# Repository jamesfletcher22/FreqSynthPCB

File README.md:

# FreqSynthPCB
A PCB Design for an Si5351A Frequency Synthesiser with Manual Control

This is a PCB I designed for a Si5351a Frequency Synthesiser. It can generate a clock at any arbitrary frequency with 1KHz resolution up to 125MHz.
Control is done using a ATMEGA328-PB. 
There is a rotary encoder to control the frequency at the output, along with an OLED for displaying the selected frequency

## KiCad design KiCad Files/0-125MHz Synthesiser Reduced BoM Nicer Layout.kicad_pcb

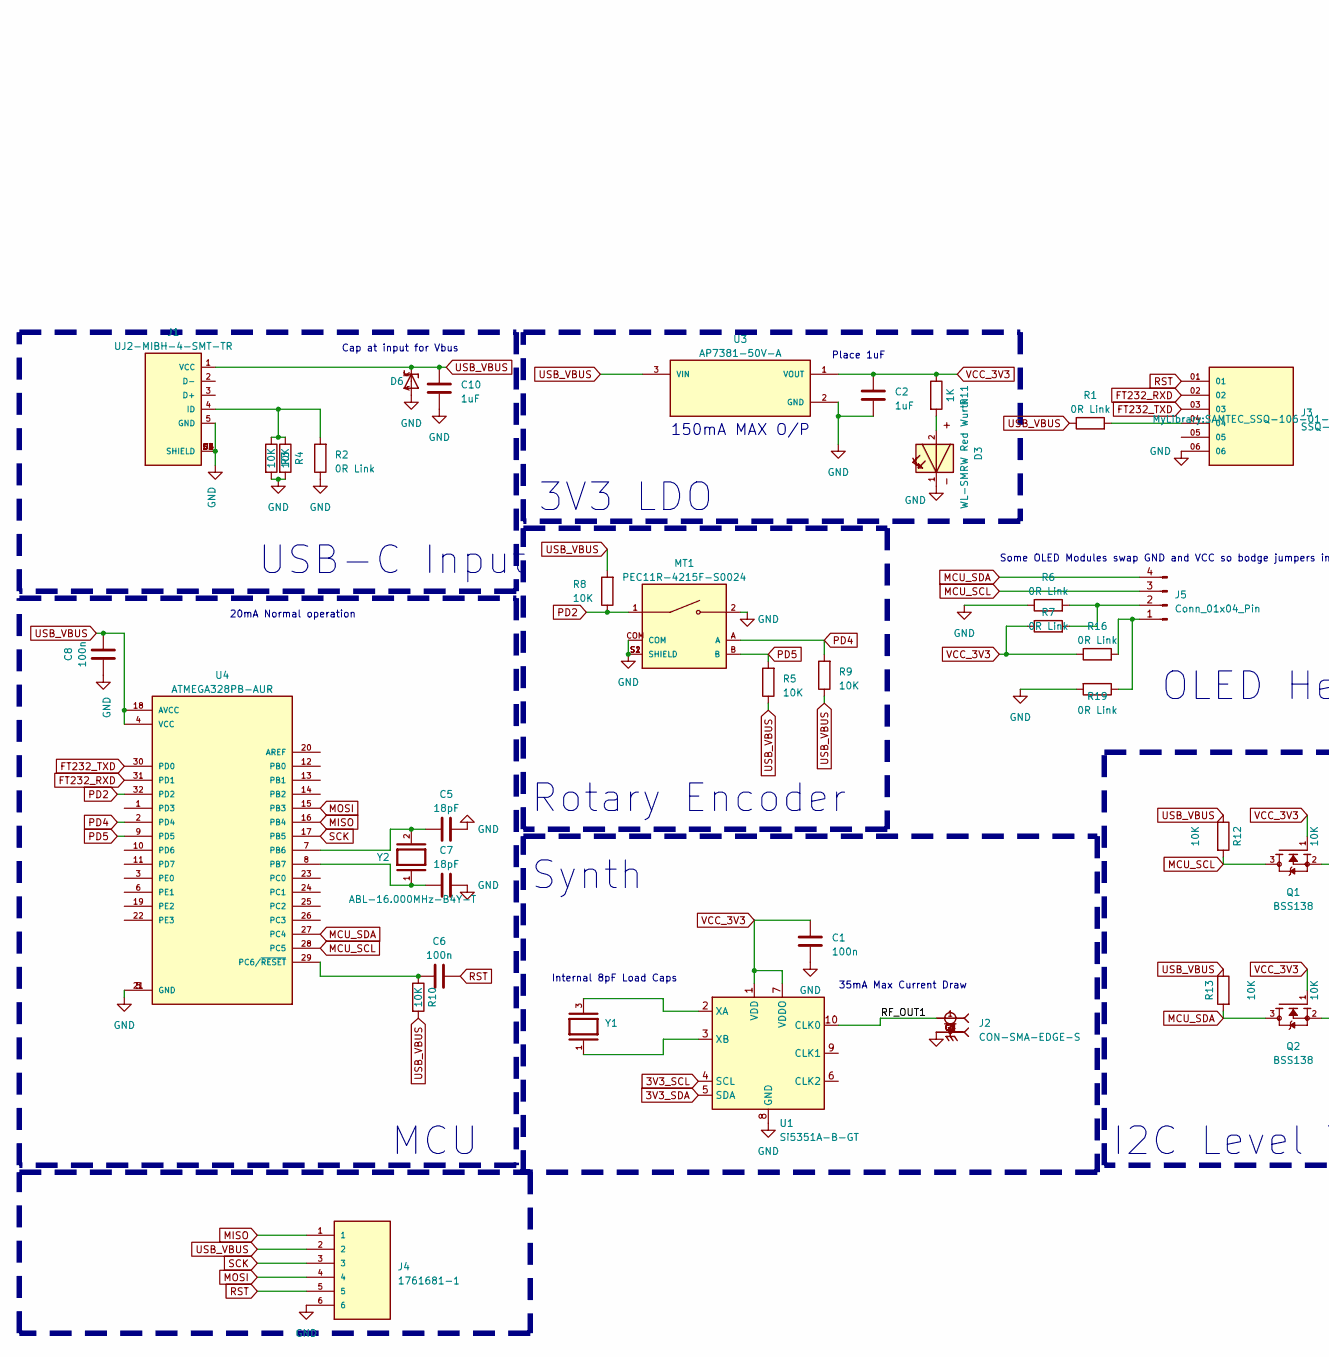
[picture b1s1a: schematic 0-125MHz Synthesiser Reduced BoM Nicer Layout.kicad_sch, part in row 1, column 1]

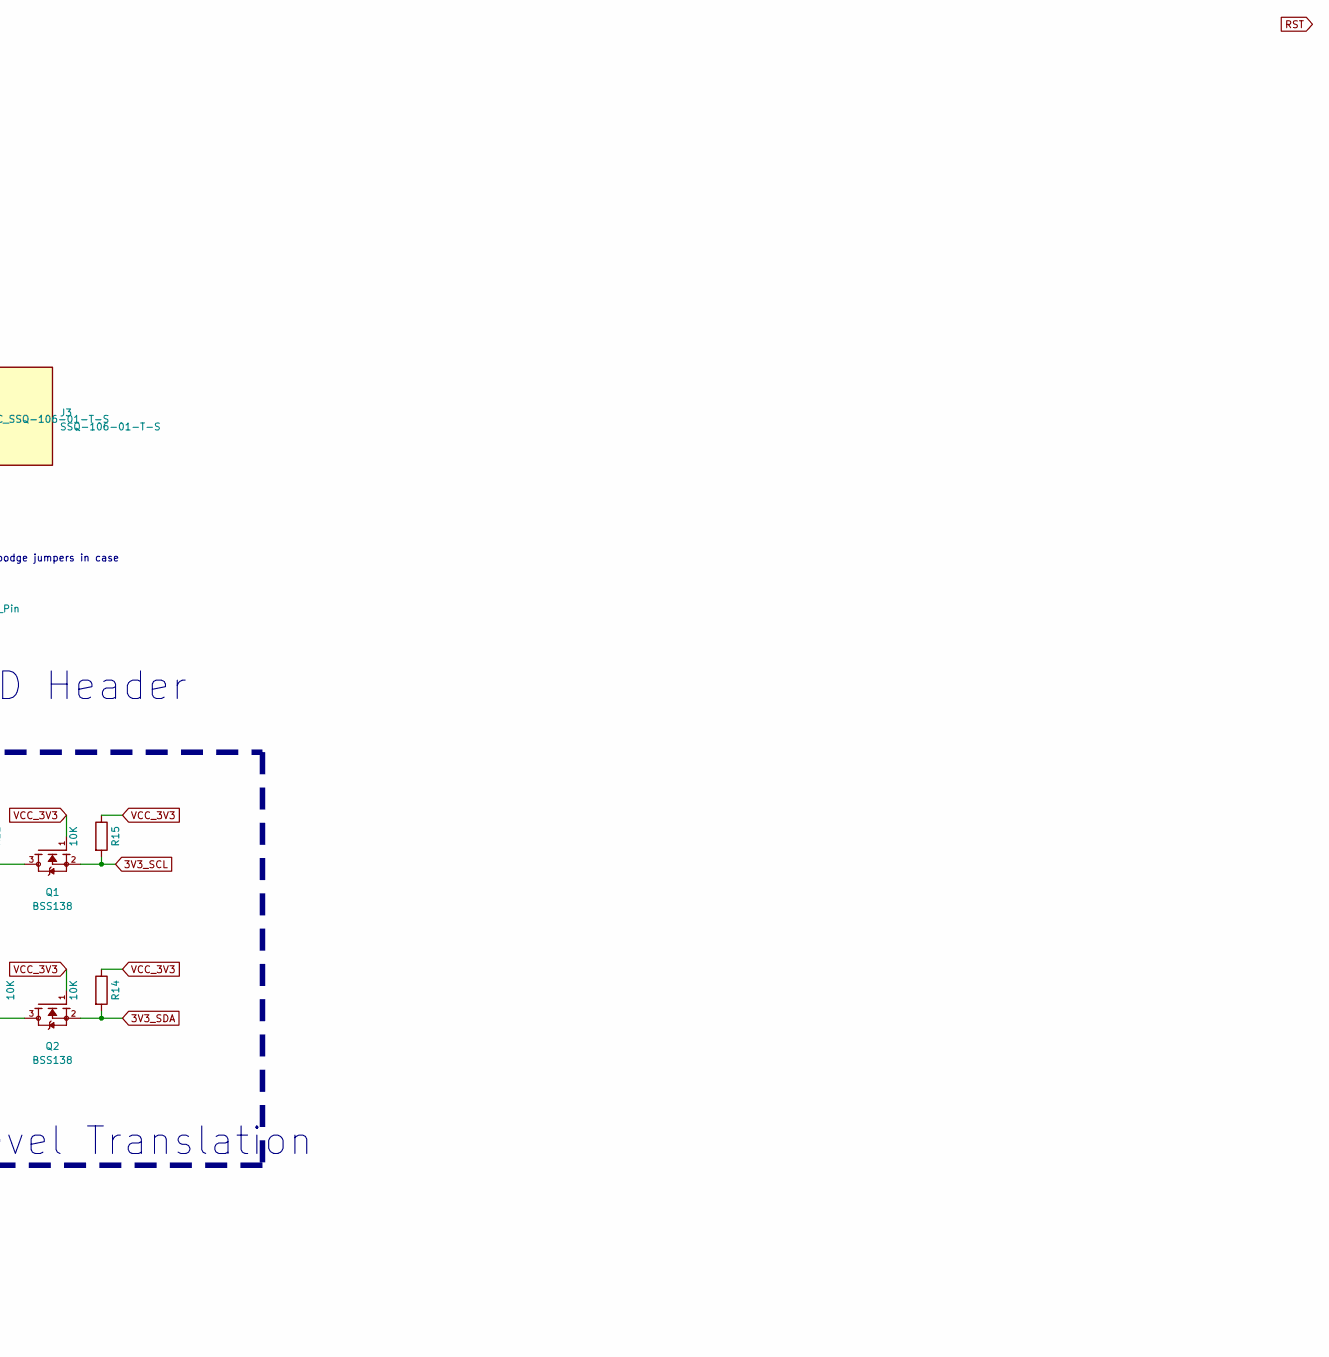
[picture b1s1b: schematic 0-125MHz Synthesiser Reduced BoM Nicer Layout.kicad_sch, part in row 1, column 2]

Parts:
C1, C6, C8: 100n; C_1206_3216Metric_Pad1.33x1.80mm_HandSolder
C2, C10: 1uF; C_1206_3216Metric_Pad1.33x1.80mm_HandSolder
C5, C7: 18pF; C_1206_3216Metric_Pad1.33x1.80mm_HandSolder
D3: WL-SMRW Red Wurth; WL-SMRW-1206-RECT
D6: ESD5Z6.0T1G; SOD-523
J1: UJ2-MIBH-4-SMT-TR; CUIDEVICES_UJ2-MIBH-4-SMT-TR; PARTREV 1.01
J2: CON-SMA-EDGE-S; RFSOLUTIONS_CON-SMA-EDGE-S; PARTREV 1
J3: SSQ-106-01-T-S; SAMTEC_SSQ-106-01-T-S; PARTREV R
J4: 1761681-1; PinHeader_2x03_P2.54mm_Vertical; PARTREV R
J5: Conn_01x04_Pin; PinHeader_1x04_P2.54mm_Vertical
MT1: PEC11R-4215F-S0024; XDCR_PEC11R-4215F-S0024; PARTREV Rev. 09/19
Q1, Q2: BSS138; SOT95P240X111-3N
R1, R2, R6, R7, R16, R19: 0R Link; SolderJumper-2_P1.3mm_Open_RoundedPad1.0x1.5mm
R3, R4, R5, R8, R9, R10, R12, R13, R14, R15: 10K; R_1206_3216Metric_Pad1.30x1.75mm_HandSolder
R11: 1K; R_1206_3216Metric_Pad1.30x1.75mm_HandSolder
U1: Si5351A-B-GT; MSOP-10_3x3mm_P0.5mm
U3: AP7381-50V-A; TO92254P480H8703; PARTREV 3 - 2
U4: ATMEGA328PB-AUR; QFP80P900X900X120-32N; PARTREV NA
Y1: XRCGB25M000F2P00R0; OSC_XRCGB25M000F2P00R0; PARTREV N/A
Y2: ABL-16.000MHz-B4Y-T; XTAL_HC49P488W46L1150T500H350; PARTREV 03.27.2018

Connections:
3V3_SCL: Q1.2, R15.2, U1.4 (SCL)
3V3_SDA: Q2.2, R14.2, U1.5 (SDA)
/RF_OUT1: J2.1, U1.10 (CLK0)
FT232_RXD: J3.02, U4.31 (PD1)
FT232_TXD: J3.03, U4.30 (PD0)
GND: C1.1, C2.2, C5.1, C7.1, C8.2, C10.2, D3.1, D6.A, J1.5 (GND), J1.P5 (SHIELD), J1.P6 (SHIELD), J1.S1 (SHIELD), J1.S2 (SHIELD), J1.S3 (SHIELD), J1.S4 (SHIELD), J2.G1, J2.G2, J2.G3, J2.G4, J3.06, J4.6, MT1.2, MT1.COM, MT1.S1 (SHIELD), MT1.S2 (SHIELD), R2.1, R3.2, R4.2, R6.1, R19.2, U1.8 (GND), U3.2 (GND), U4.5 (GND), U4.21 (GND)
MCU_SCL: J5.3, Q1.3, R12.2, U4.28 (PC5)
MCU_SDA: J5.4, Q2.3, R13.2, U4.27 (PC4)
MISO: J4.1, U4.16 (PB4)
MOSI: J4.4, U4.15 (PB3)
unnamed: D3.2, R11.2
unnamed: J1.4 (ID), R2.2, R3.1, R4.1
unnamed: J3.04, R1.2
unnamed: J5.1, R16.2, R19.1
unnamed: J5.2, R6.2, R7.2
unnamed: U1.2 (XA), Y1.3
unnamed: U1.3 (XB), Y1.1
unnamed: C5.2, U4.7 (PB6), Y2.2
unnamed: C7.2, U4.8 (PB7), Y2.1
unnamed: C6.1, R10.1, U4.29 (PC6/~RESET)
PD2: MT1.1, R8.1, U4.32 (PD2)
PD4: MT1.A, R9.2, U4.2 (PD4)
PD5: MT1.B, R5.2, U4.9 (PD5)
RST: C6.2, J3.01, J4.5
SCK: J4.3, U4.17 (PB5)
USB_VBUS: C8.1, C10.1, D6.K, J1.1 (VCC), J4.2, R1.1, R5.1, R8.2, R9.1, R10.2, R12.1, R13.1, U3.3 (VIN), U4.4 (VCC), U4.18 (AVCC)
VCC_3V3: C1.2, C2.1, Q1.1, Q2.1, R7.1, R11.1, R14.1, R15.1, R16.1, U1.1 (VDD), U1.7 (VDDO), U3.1 (VOUT)

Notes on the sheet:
MCU
OLED Header
I2C Level Translation
Some OLED Modules swap GND and VCC so bodge jumpers in case
3V3 LDO
150mA MAX O/P
20mA Normal operation
35mA Max Current Draw
Internal 8pF Load Caps
USB-C Input
Cap at input for Vbus
Synth
Rotary Encoder
Place 1uF

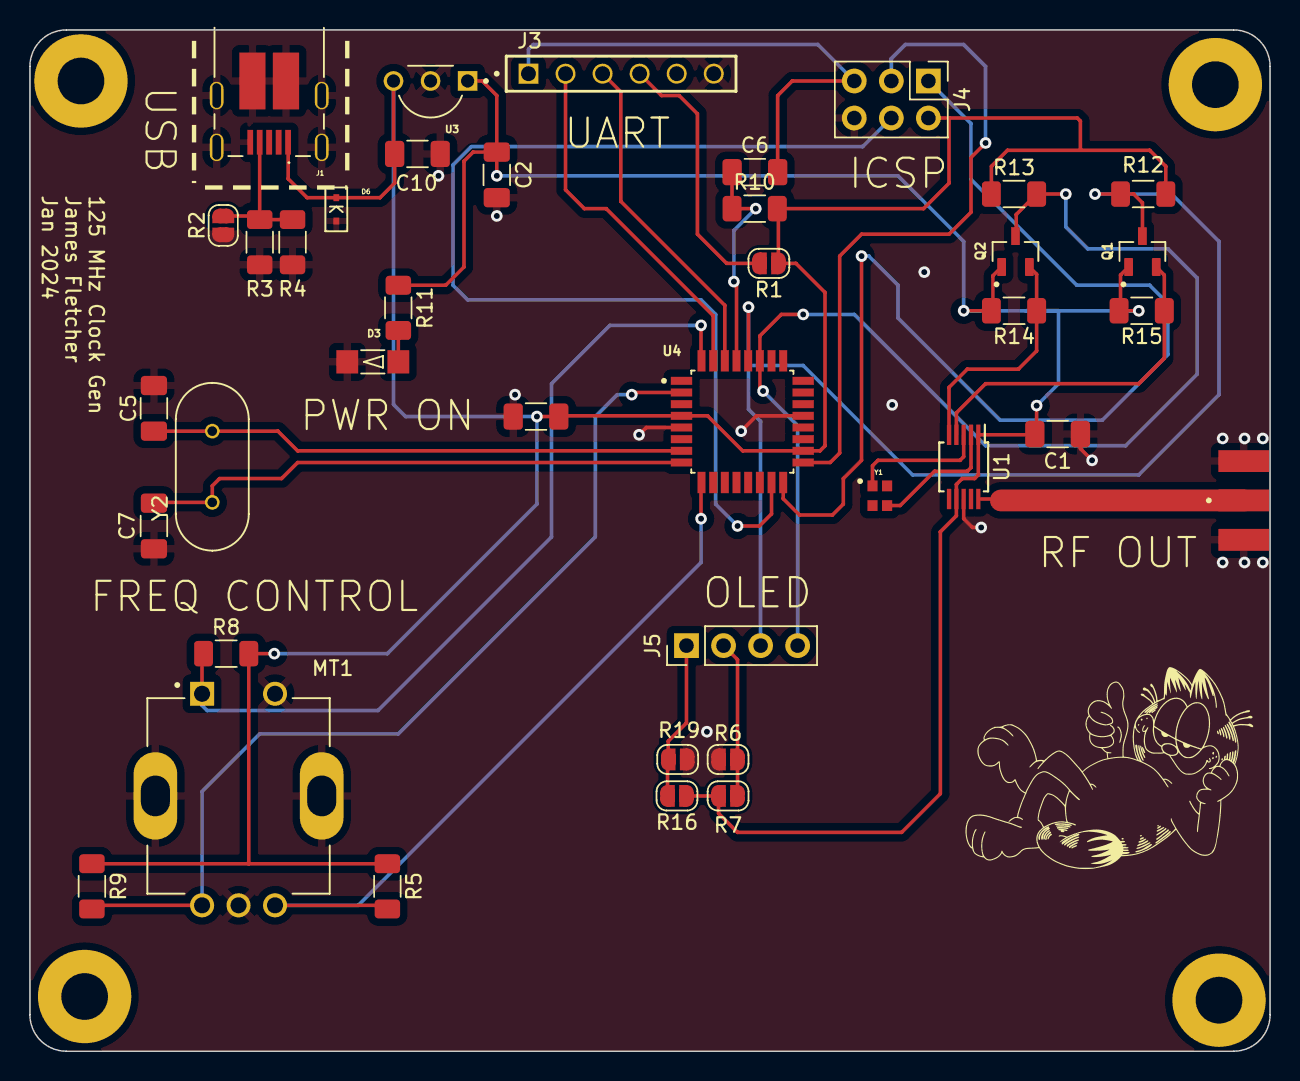
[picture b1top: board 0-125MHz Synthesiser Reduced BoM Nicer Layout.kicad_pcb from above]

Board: 2 copper layers, 85.0 x 70.0 mm, 39 parts (0 on the bottom side), 27 nets.
